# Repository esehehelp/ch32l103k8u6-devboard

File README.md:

# ch32l103k8u6-devboard

* **サイズ**: 48.3mm x 12.7mm
* **MCU**: CH32L103K8U6
* **電源**:
* JW5026 同期整流DCDC (5V/1A出力)
* XC6206 (3.3V/200mA出力)

* **特徴**:
* USB PD対応 (最大20V入力)
* ブレッドボードに最適 (12.7mm幅)

* **ライセンス**: MIT License

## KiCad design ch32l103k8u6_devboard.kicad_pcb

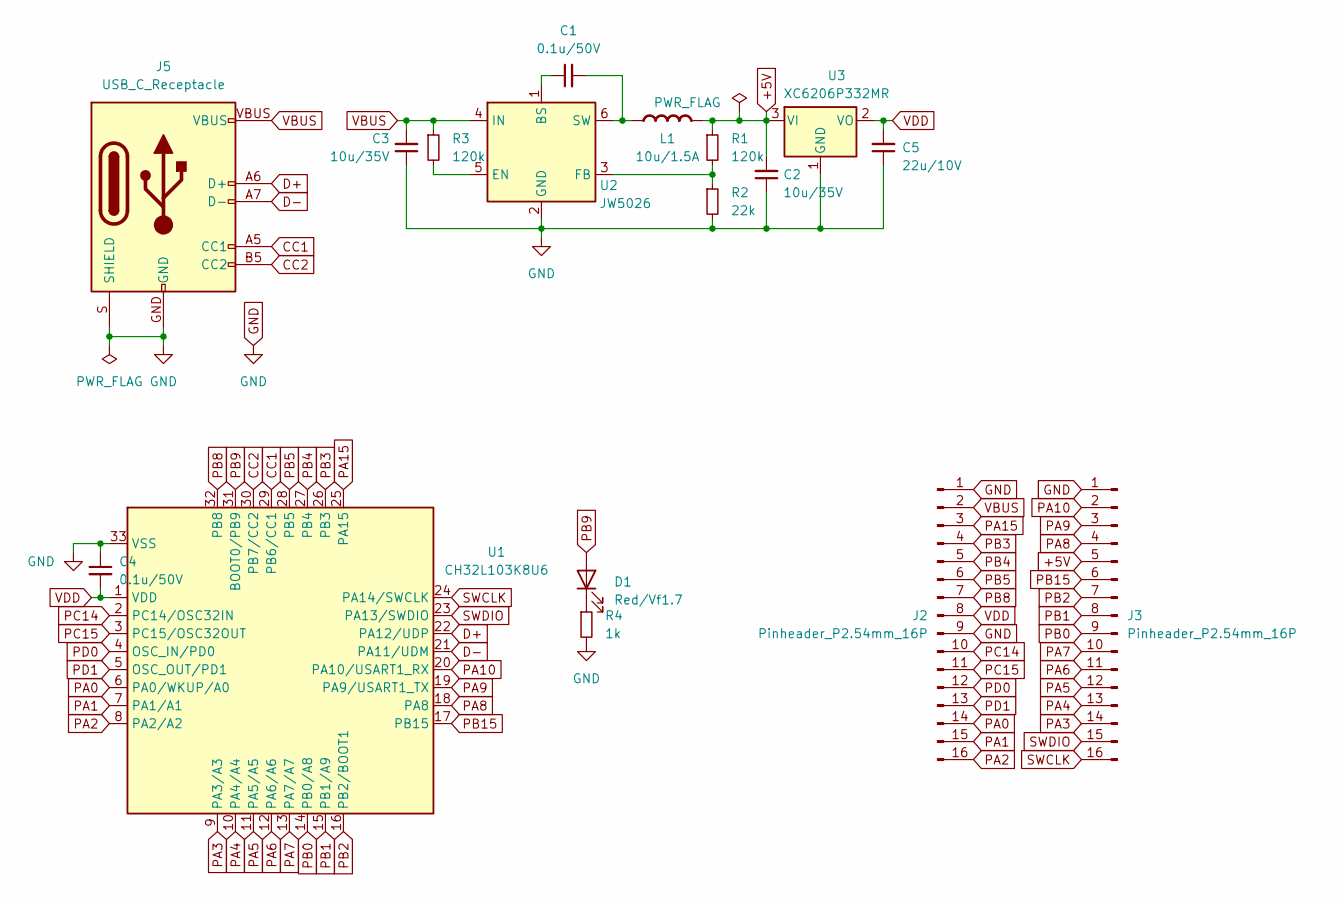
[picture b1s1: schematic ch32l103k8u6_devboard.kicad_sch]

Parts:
C1, C4: 0.1u/50V; C_0603_1608Metric
C2, C3: 10u/35V; C_0603_1608Metric
C5: 22u/10V; C_0603_1608Metric
D1: Red/Vf1.7; LED_0603_1608Metric
J2, J3: Pinheader_P2.54mm_16P; PinHeader_1x16_P2.54mm_Vertical
J5: USB_C_Receptacle; USB-C_16-HandSolder; LCSC C393939
L1: 10u/1.5A; L_Changjiang_FNR4020S; Rating A
R1, R3: 120k; R_0603_1608Metric
R2: 22k; R_0603_1608Metric
R4: 1k; R_0603_1608Metric
U1: CH32L103K8U6; QFN-32-1EP_4x4mm_P0.4mm_EP2.9x2.9mm
U2: JW5026; SOT-23-6; LCSC C2935411
U3: XC6206P332MR; SOT-23-3

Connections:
+5V: C2.2, J3.5, L1.2 (-), R1.1, U3.3 (VI)
CC1: J5.A5 (CC1), U1.29 (PB6/CC1)
CC2: J5.B5 (CC2), U1.30 (PB7/CC2)
D+: J5.A6 (D+), J5.B6 (D+), U1.22 (PA12/UDP)
D-: J5.A7 (D-), J5.B7 (D-), U1.21 (PA11/UDM)
GND: C2.1, C3.1, C4.1, C5.1, J2.1, J2.9, J3.1, J5.GND, J5.S (SHIELD), R2.2, R4.2, U1.33 (VSS), U2.2 (GND), U3.1 (GND)
unnamed: D1.1 (K), R4.1
unnamed: C1.2, L1.1 (+), U2.6 (SW)
unnamed: C1.1, U2.1 (BS)
unnamed: R3.2, U2.5 (EN)
unnamed: R1.2, R2.1, U2.3 (FB)
PA0: J2.14, U1.6 (PA0/WKUP/A0)
PA1: J2.15, U1.7 (PA1/A1)
PA2: J2.16, U1.8 (PA2/A2)
PA3: J3.14, U1.9 (PA3/A3)
PA4: J3.13, U1.10 (PA4/A4)
PA5: J3.12, U1.11 (PA5/A5)
PA6: J3.11, U1.12 (PA6/A6)
PA7: J3.10, U1.13 (PA7/A7)
PA8: J3.4, U1.18 (PA8)
PA9: J3.3, U1.19 (PA9/USART1_TX)
PA10: J3.2, U1.20 (PA10/USART1_RX)
PA15: J2.3, U1.25 (PA15)
PB0: J3.9, U1.14 (PB0/A8)
PB1: J3.8, U1.15 (PB1/A9)
PB2: J3.7, U1.16 (PB2/BOOT1)
PB3: J2.4, U1.26 (PB3)
PB4: J2.5, U1.27 (PB4)
PB5: J2.6, U1.28 (PB5)
PB8: J2.7, U1.32 (PB8)
PB9: D1.2 (A), U1.31 (BOOT0/PB9)
PB15: J3.6, U1.17 (PB15)
PC14: J2.10, U1.2 (PC14/OSC32IN)
PC15: J2.11, U1.3 (PC15/OSC32OUT)
PD0: J2.12, U1.4 (OSC_IN/PD0)
PD1: J2.13, U1.5 (OSC_OUT/PD1)
SWCLK: J3.16, U1.24 (PA14/SWCLK)
SWDIO: J3.15, U1.23 (PA13/SWDIO)
VBUS: C3.2, J2.2, J5.VBUS, R3.1, U2.4 (IN)
VDD: C4.2, C5.2, J2.8, U1.1 (VDD), U3.2 (VO)

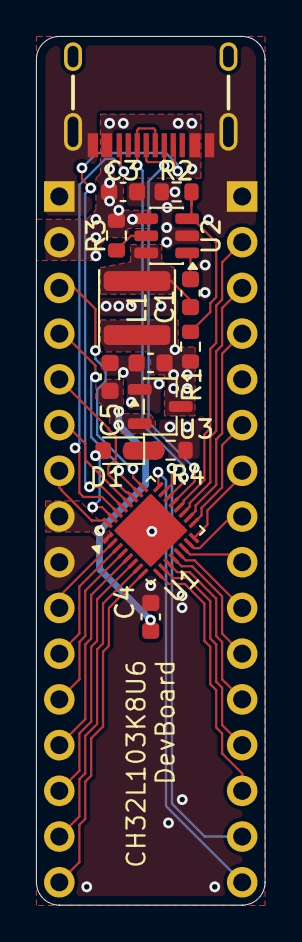
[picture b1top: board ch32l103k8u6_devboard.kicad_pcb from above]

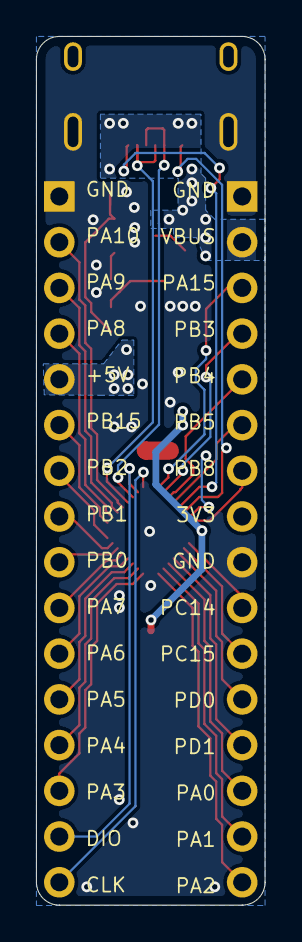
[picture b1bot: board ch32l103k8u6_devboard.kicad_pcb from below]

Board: 2 copper layers, 12.7 x 48.3 mm, 17 parts (2 on the bottom side), 40 nets.

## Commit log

2026-02-26 Add README.md
2026-02-26 Add MIT License to the project
